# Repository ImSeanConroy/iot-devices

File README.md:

# IoT Devices

**A monorepo for AWS IoT experiments and hardware prototypes** built around ESP32 boards, MQTT messaging, custom PCB designs, and a local dashboard for visualizing device events.

This repository contains end-to-end building blocks for connected devices:

- ESP32 firmware publishers/subscribers
- AWS IoT Core infrastructure defined with Terraform
- KiCad PCB projects for multiple device types
- A Blink dashboard (Node.js backend + React frontend)

## Table of Contents

- [Monorepo Structure](#monorepo-structure)
- [Getting Started](#getting-started)
  - [1. Clone the Repository](#1-clone-the-repository)
  - [2. Provision AWS IoT Infrastructure](#2-provision-aws-iot-infrastructure) 
  - [3. Configure and Flash Firmware](#3-configure-and-flash-firmware)
  - [4. Run the Blink Dashboard](#4-run-the-blink-dashboard)
  - [5. Open PCB Projects (Optional)](#5-open-pcb-projects-optional)
- [Device Topics and Roles](#device-topics-and-roles)
- [Hardware Notes](#hardware-notes)
- [Contributing](#contributing)
- [License](#license)
- [Support](#support)
- [Acknowledgments](#acknowledgments)

## Monorepo Structure

- `Firmware/` - Arduino firmware for Blink, Generic, Door Sensor, GPS, and Temperature device variants.
- `Terraform/` - Infrastructure as code for AWS IoT Things, certificates, and policies.
- `Dashboard/` - Local dashboards built with node and express.
- `PCB/` - KiCad projects for Blink, Door Sensor, GPS, and Temperature hardware.
- `Case/` - Mechanical/case assets.

## Getting Started

Before starting, install:

| Tool | Purpose | Link |
| --- | --- | --- |
| Node.js (>=18) | Dashboard backend/frontend runtime | [Download](https://nodejs.org/) |
| npm | JavaScript package manager | [Download](https://www.npmjs.com/) |
| Terraform | AWS IoT infrastructure provisioning | [Install Guide](https://developer.hashicorp.com/terraform/install) |
| AWS CLI | AWS authentication and account setup | [AWS CLI](https://aws.amazon.com/cli/) |
| Arduino IDE | Build/upload firmware | [Arduino IDE](https://www.arduino.cc/en/software) |
| KiCad | Open PCB projects | [KiCad](https://www.kicad.org/) |

### 1. Clone the Repository

```bash
git clone git@github.com:ImSeanConroy/iot-devices.git
cd iot-devices
```

### 2. Provision AWS IoT Infrastructure

1. Configure AWS credentials (or run `aws configure`).

```bash
export AWS_ACCESS_KEY_ID=<your-access-key>
export AWS_SECRET_ACCESS_KEY=<your-secret-key>
export AWS_REGION=<your-region>
```

2. Deploy infrastructure.

```bash
cd Terraform
terraform init
terraform apply
```

3. Retrieve generated values.

```bash
terraform output root_ca_url
terraform output device_client_ids
terraform output device_certificates
terraform output device_private_keys
```

### 3. Configure and Flash Firmware

1. Choose a firmware target, for example:
   - `Firmware/BlinkPublisher/BlinkPublisher.ino`
   - `Firmware/BlinkSubscriber/BlinkSubscriber.ino`
   - `Firmware/GenericPublisher/GenericPublisher.ino`
   - `Firmware/GenericSubscriber/GenericSubscriber.ino`

2. In the selected folder, copy `secrets.h.template` to `secrets.h`.

3. Update `secrets.h` with:
   - `WIFI_SSID` and `WIFI_PASSWORD`
   - `AWS_IOT_ENDPOINT`
   - Root CA certificate
   - Device certificate and private key

4. Compile and upload from Arduino IDE.

### 4. Run the Blink Dashboard

The Blink dashboard lives in `Dashboard/blink/`.

1. Prepare backend cert files:

```bash
cd Dashboard/blink/backend/src/certs
cp cert.pem.example cert.pem
cp key.pem.example key.pem
cp rootCA.pem.example rootCA.pem
```

2. Start backend (default `http://localhost:3000`).

```bash
cd ../../
npm install
npm run dev
```

3. Start frontend (Vite, usually `http://localhost:5173`).

```bash
cd ../frontend
npm install
npm run dev
```

### 5. Open PCB Projects (Optional)

Open any KiCad project in `PCB/`, for example:

- `PCB/IoT_Devices_Blink/IoT_Devices_Blink.kicad_pro`
- `PCB/-IoT_Devices_Door_Sensor/`
- `PCB/-IoT_Devices_GPS/`
- `PCB/-IoT_Devices_Temperature_Sensor/`

## Device Topics and Roles

Terraform currently defines devices in `Terraform/main.tf`.

- Active by default:
  - `door_sensor_publisher` -> topic `iot-devices/door-sensor`
- Present but commented out:
  - Blink publisher/subscriber/dashboard
  - Generic publisher/subscriber
  - Temperature publisher
  - GPS publisher

To enable additional roles, uncomment the corresponding entries in `local.iot_devices` and re-run `terraform apply`.

## Hardware Notes

- Firmware targets Seeed Studio XIAO ESP32C3-class boards.
- Blink subscriber firmware expects a WS2812-compatible LED connected to the configured pin.
- PCB designs are maintained in KiCad and can be exported for fabrication.

## Contributing

Contributions are welcome. Please open an issue or fork the repository, create a new branch (`feature/your-feature-name`) and submit a pull request for any enhancements or bug fixes.

## License

This project is licensed under the MIT License - see the [LICENSE](LICENSE) file for information.

## Support

If you are having problems, please let me know by [raising a new issue](https://github.com/ImSeanConroy/iot-devices/issues/new/choose).

## Acknowledgments

This project was made possible thanks to the following resources:

- [AWS re:Post](https://repost.aws/questions/QUxlg-arOrTcaxFAdNEj7hqA/lambda-publish-a-mqtt-message-to-iot-core-inside-a-lambda-function-with-node-and-sdk-3) - Publish a MQTT Message to IOT Core inside a Lambda function with Node and SDK 3
- [AWS Samples](https://github.com/aws-samples/aws-iot-esp32-arduino-examples) - Several Arduino examples for AWS IoT projects using ESP32.

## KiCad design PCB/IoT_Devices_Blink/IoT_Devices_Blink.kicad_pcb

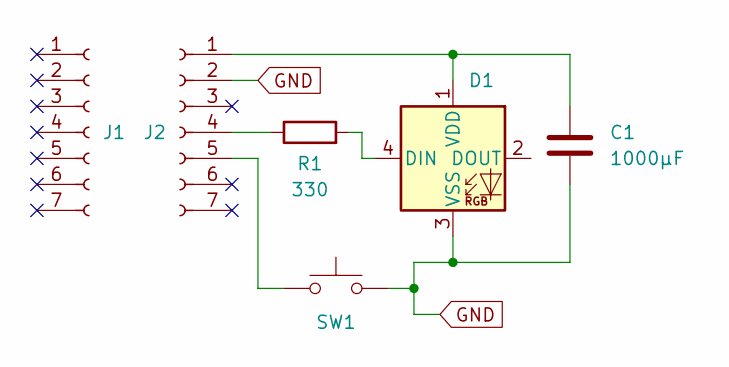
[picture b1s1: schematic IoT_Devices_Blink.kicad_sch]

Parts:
C1: 1000µF; CP_Radial_D8.0mm_P3.80mm
D1: WS2812B; WS2812D
J1, J2: Conn_01x07_Socket; PinSocket_1x07_P2.54mm_Vertical
R1: 330; R_Axial_DIN0204_L3.6mm_D1.6mm_P5.08mm_Horizontal
SW1: SW_Push; SW_PUSH_6mm

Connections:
GND: C1.2, D1.3 (VSS), J2.2, SW1.2
unnamed: D1.4 (DIN), R1.2
unnamed: C1.1, D1.1 (VDD), J2.1
unnamed: J2.4, R1.1
unnamed: J2.5, SW1.1

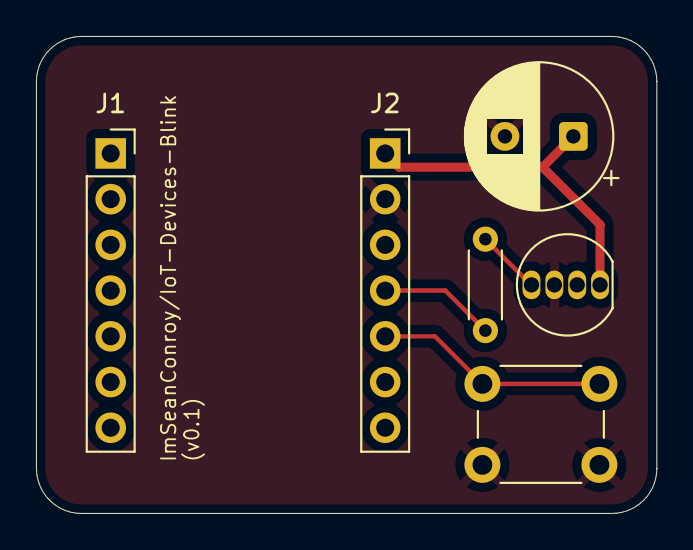
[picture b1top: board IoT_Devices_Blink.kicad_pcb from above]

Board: 2 copper layers, 34.5 x 26.5 mm, 6 parts (0 on the bottom side), 5 nets.

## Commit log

2026-03-16 Create generic publisher and subscriber
2026-03-17 Create blink publisher and subscriber
2026-03-17 Convert blink firmware to use ws2b12
2026-03-18 Create blink pcb
2026-03-22 Create basic blink iot dashboard
2026-03-23 Create door sensor firmware
